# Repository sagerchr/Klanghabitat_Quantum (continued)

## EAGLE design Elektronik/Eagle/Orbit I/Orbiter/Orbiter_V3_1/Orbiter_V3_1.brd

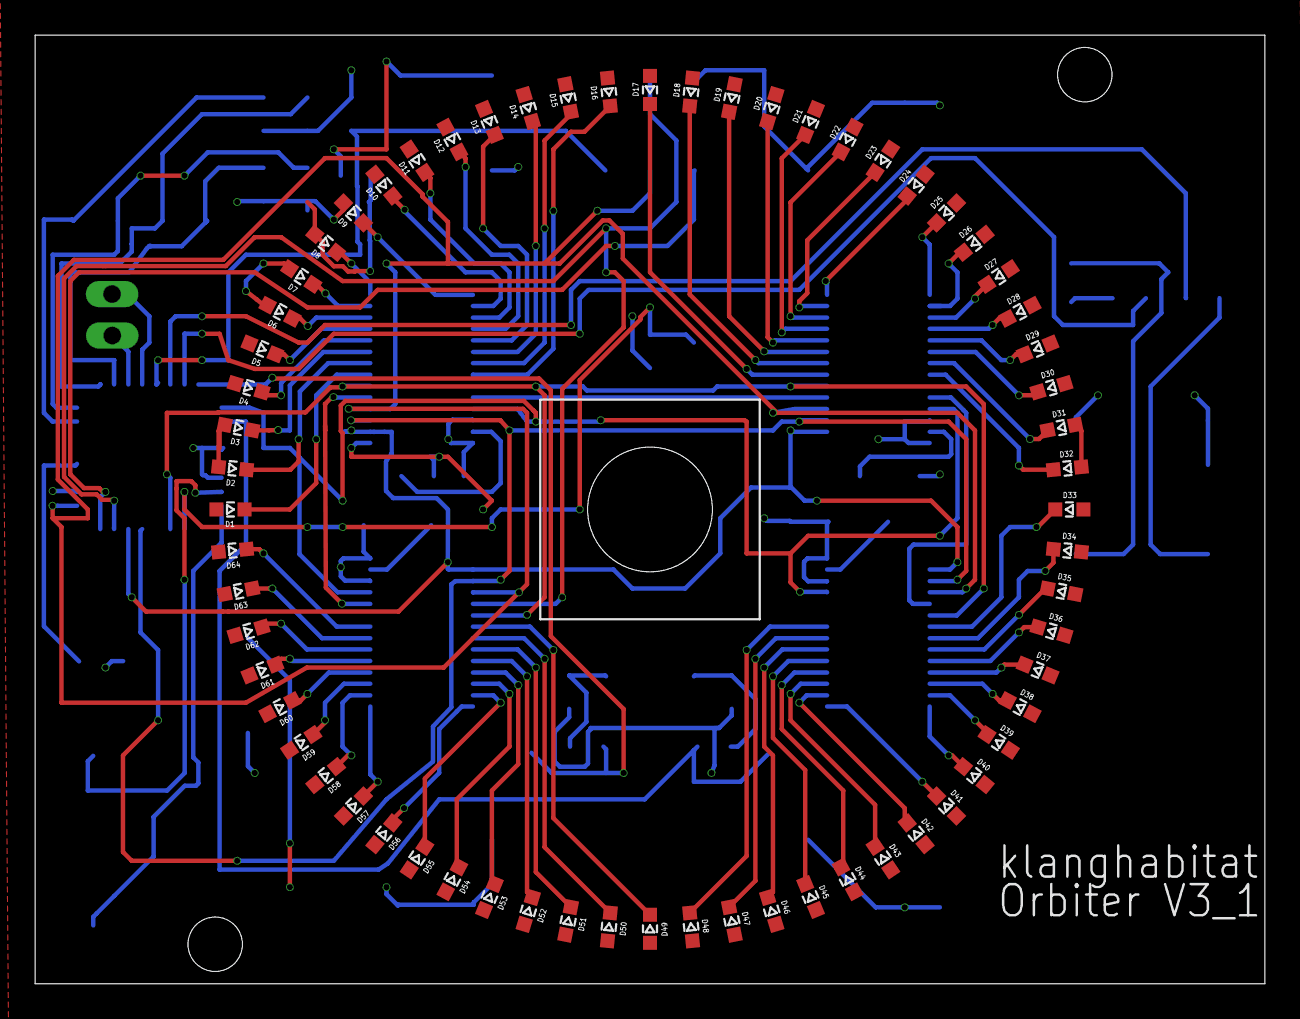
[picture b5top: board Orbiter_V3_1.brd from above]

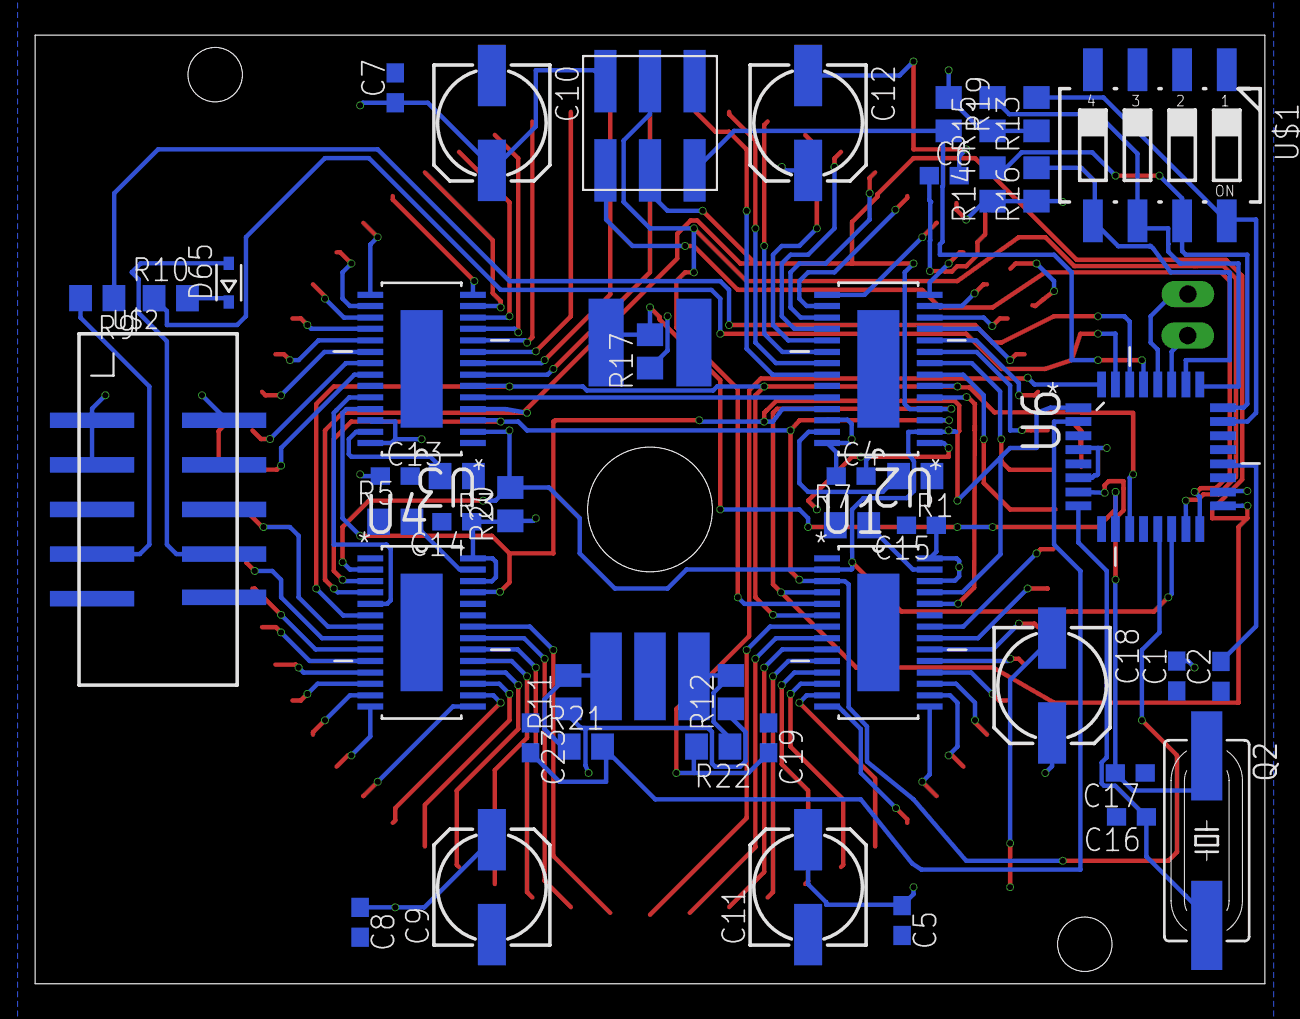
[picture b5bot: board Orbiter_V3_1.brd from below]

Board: 2 copper layers, 70.0 x 54.0 mm, 113 parts (46 on the bottom side), 100 nets.

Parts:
A4, A5: TPTHT; THT_PIN
C1: 1uF; C0603
C2: 100nF; C0603
C4, C5, C6, C7, C8, C13, C14, C15: 100n; C0603
C9, C10, C11, C12: 10u; 153CLV-0605
C16, C17: 22p; C0603
C18: 4,7uF/16V; 153CLV-0605
C19, C23: 10nF; C0603
D1, D2, D3, D4, D5, D6, D7, D8, D9, D10, D11, D12, D13, D14, D15, D16, D17, D18, D19, D20, D21, D22, D23, D24, D25, D26, D27, D28, D29, D30, D31, D32, D33, D34, D35, D36, D37, D38, D39, D40, D41, D42, D43, D44, D45, D46, D47, D48, D49, D50, D51, D52, D53, D54, D55, D56, D57, D58, D59, D60, D61, D62, D63, D64: SMD_LED_0603; WL-SMCW_0603
D65: 4148; SOD323-R
Q2: 16MHZ; SM49
R1, R3, R5, R7: 2k; R0805
R9, R10: 1k; R0805
R11, R12, R13, R14, R15, R16, R17, R19, R20, R21, R22: 10k; R0805
U1, U2, U3, U4: TLC5940; SOP65P640X120-29N
U6: ATMEGA328; QFP80P900X900X120-32N
U$1: 4PIN_DIP; CTS-219-04
U$2: 10PIN_HEADER_SMD; 87832-10
U$3: 6PIN_HEADER_SMD_OPEN
U$4: BOURNS_ENCODER; BOURNS_ENCODER_SMD

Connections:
A0: R13.2, U6.23, U$1.8
A1: R14.2, U6.24, U$1.7
A2: R15.2, U6.25, U$1.6
A3: R16.2, U6.26, U$1.5
A4: A4.P$1, U6.27
A5: A5.P$1, U6.28
D0/RX: R9.1, U6.30
D1/TX: R10.1, U6.31
D2/TB: C19.2, R22.2, U6.32
D3/GSCLK: U1.25, U2.25, U3.25, U4.25, U6.1
D4/TA: C23.2, R21.2, U6.2
D6/SWITCH: R17.2, U6.10, U$4.S2
D7/MODE: U1.6, U2.6, U3.6, U4.6, U6.11
D9/XLAT: U1.3, U2.3, U3.3, U4.3, U6.13
D10/BLANK: R20.2, U1.2, U2.2, U3.2, U4.2, U6.14
D11/MOSI/SIN: U1.5, U6.15, U$3.4
D12/MISO: U6.16, U$3.1
D13/SCK: U1.4, U2.4, U3.4, U4.4, U6.17, U$3.3
GND: C1.1, C2.1, C4.2, C5.2, C6.2, C7.2, C8.2, C9.-, C10.-, C11.-, C12.-, C13.2, C14.2, C15.2, C16.2, C17.1, C18.-, C19.1, C23.1, R1.1, R3.1, R5.1, R7.1, U1.1, U2.1, U3.1, U4.1, U6.3, U6.5, U6.21, U$1.1, U$1.2, U$1.3, U$1.4, U$2.5, U$2.6, U$2.9, U$2.10, U$3.6, U$4.S1, U$4.VDC
IREF_U1: R1.2, U2.27
IREF_U2: R3.2, U3.27
IREF_U3: R5.2, U4.27
IREF_U4: R7.2, U1.27
unnamed: D1.1, U2.7
unnamed: U1.24, U2.5
unnamed: D2.1, U2.8
unnamed: D8.1, U2.14
unnamed: D3.1, U2.9
unnamed: D9.1, U2.15
unnamed: D4.1, U2.10
unnamed: D10.1, U2.16
unnamed: D5.1, U2.11
unnamed: D6.1, U2.12
unnamed: D7.1, U2.13
unnamed: D11.1, U2.17
unnamed: D12.1, U2.18
unnamed: D13.1, U2.19
unnamed: D14.1, U2.20
unnamed: D15.1, U2.21
unnamed: D16.1, U2.22
unnamed: D17.1, U3.7
unnamed: D18.1, U3.8
unnamed: D19.1, U3.9
unnamed: D20.1, U3.10
unnamed: D21.1, U3.11
unnamed: D22.1, U3.12
unnamed: D23.1, U3.13
unnamed: D24.1, U3.14
unnamed: D25.1, U3.15
unnamed: D26.1, U3.16
unnamed: D27.1, U3.17
unnamed: D28.1, U3.18
unnamed: D29.1, U3.19
unnamed: D30.1, U3.20
unnamed: D31.1, U3.21
unnamed: D32.1, U3.22
unnamed: D33.1, U4.7
unnamed: D34.1, U4.8
unnamed: D35.1, U4.9
unnamed: D36.1, U4.10
unnamed: D37.1, U4.11
unnamed: D38.1, U4.12
unnamed: D39.1, U4.13
unnamed: D40.1, U4.14
unnamed: D41.1, U4.15
unnamed: D42.1, U4.16
unnamed: D43.1, U4.17
unnamed: D44.1, U4.18
unnamed: D45.1, U4.19
unnamed: D46.1, U4.20
unnamed: D47.1, U4.21
unnamed: D48.1, U4.22
unnamed: D49.1, U1.7
unnamed: D50.1, U1.8
unnamed: D51.1, U1.9
unnamed: D52.1, U1.10
unnamed: D53.1, U1.11
unnamed: D54.1, U1.12
unnamed: D55.1, U1.13
unnamed: D56.1, U1.14
unnamed: D57.1, U1.15
unnamed: D58.1, U1.16
unnamed: D59.1, U1.17
unnamed: D60.1, U1.18
unnamed: D61.1, U1.19
unnamed: D62.1, U1.20
unnamed: D63.1, U1.21
unnamed: D64.1, U1.22
unnamed: D65.C, R10.2
unnamed: C17.2, Q2.1, U6.7
unnamed: C16.1, Q2.2, U6.8
unnamed: C2.2, U6.20
RESET: R19.2, U6.29, U$3.5
RX: R9.2, U$2.7
SIN_U2: U2.24, U3.5
SIN_U3: U3.24, U4.5
TA: R11.2, R21.1, U$4.TA
TB: R12.2, R22.1, U$4.TB
TX: D65.A, U$2.8
VCC: C1.2, C4.1, C5.1, C6.1, C7.1, C8.1, C9.+, C10.+, C11.+, C12.+, C13.1, C14.1, C15.1, C18.+, D1.2, D2.2, D3.2, D4.2, D5.2, D6.2, D7.2, D8.2, D9.2, D10.2, D11.2, D12.2, D13.2, D14.2, D15.2, D16.2, D17.2, D18.2, D19.2, D20.2, D21.2, D22.2, D23.2, D24.2, D25.2, D26.2, D27.2, D28.2, D29.2, D30.2, D31.2, D32.2, D33.2, D34.2, D35.2, D36.2, D37.2, D38.2, D39.2, D40.2, D41.2, D42.2, D43.2, D44.2, D45.2, D46.2, D47.2, D48.2, D49.2, D50.2, D51.2, D52.2, D53.2, D54.2, D55.2, D56.2, D57.2, D58.2, D59.2, D60.2, D61.2, D62.2, D63.2, D64.2, R11.1, R12.1, R13.1, R14.1, R15.1, R16.1, R17.1, R19.1, R20.1, U1.26, U1.28, U2.26, U2.28, U3.26, U3.28, U4.26, U4.28, U6.4, U6.6, U6.18, U$2.1, U$2.2, U$2.3, U$3.2

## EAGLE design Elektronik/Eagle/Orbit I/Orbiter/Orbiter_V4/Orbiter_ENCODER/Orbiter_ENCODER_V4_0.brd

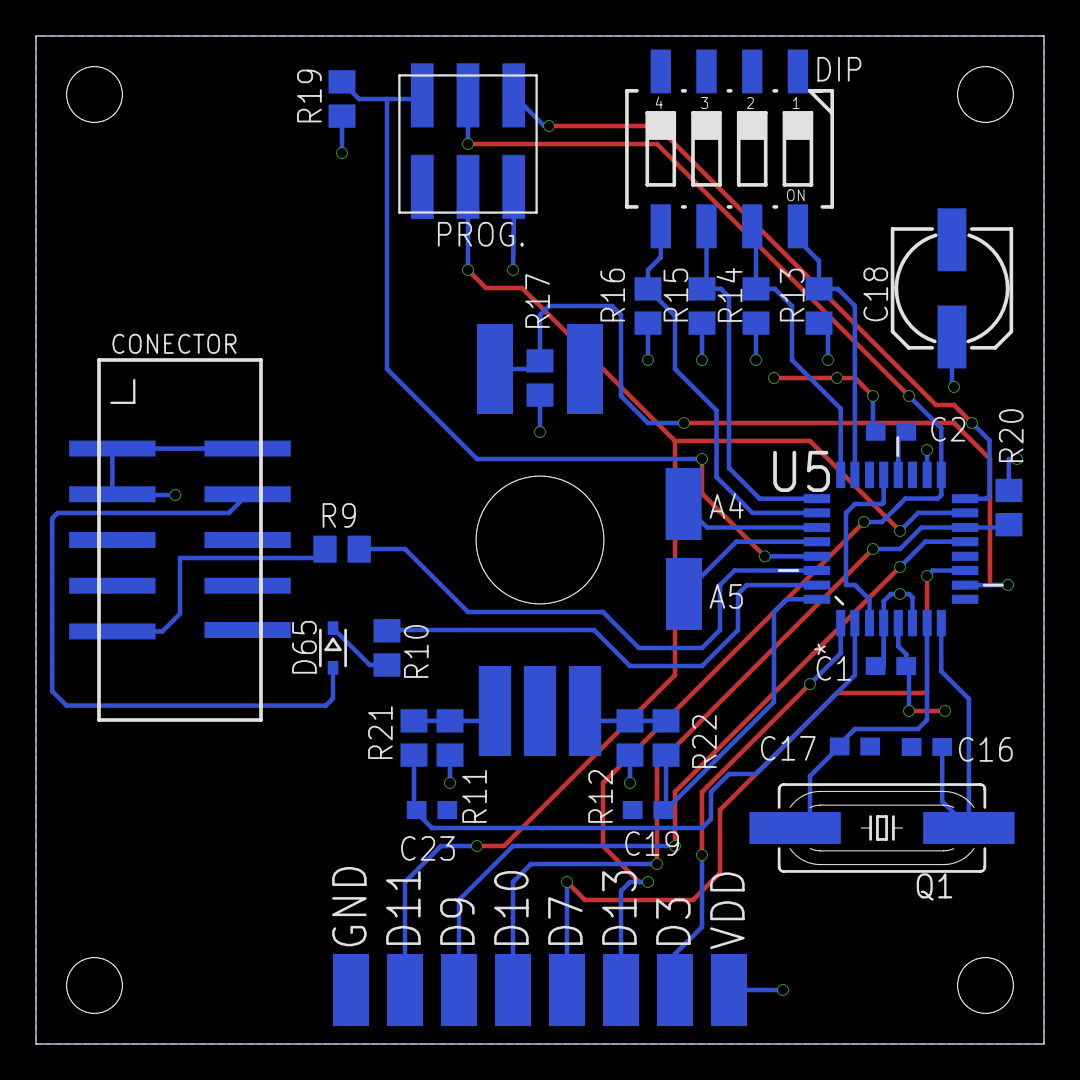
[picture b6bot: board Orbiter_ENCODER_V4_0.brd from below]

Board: 2 copper layers, 56.0 x 56.0 mm, 37 parts (36 on the bottom side), 29 nets.

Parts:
A4, A5: TP; OVAL_PAD
C1: 1uF; C0603
C2: 100nF; C0603
C16, C17: 22p; C0603
C18: 4,7uF/16V; 153CLV-0605
C19, C23: 10nF; C0603
CONECTOR: 10PIN_HEADER_SMD; 87832-10
D65: 4148; SOD323-R
DIP: 4PIN_DIP; CTS-219-04
ENC.: BOURNS_ENCODER; BOURNS_ENCODER_SMD
PROG.: 6PIN_HEADER_SMD_OPEN
Q1: 16MHZ; SM49
R9, R10: 1k; R0805
R11, R12, R13, R14, R15, R16, R17, R19, R20, R21, R22: 10k; R0805
U5: ATMEGA328; QFP80P900X900X120-32N
U$1, U$2, U$3, U$4, U$5, U$6, U$7, U$8: TP; OVAL_PAD

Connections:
A0: DIP.8, R13.2, U5.23
A1: DIP.7, R14.2, U5.24
A2: DIP.6, R15.2, U5.25
A3: DIP.5, R16.2, U5.26
A4: A4.P$1, U5.27
A5: A5.P$1, U5.28
D0/RX: R9.1, U5.30
D1/TX: R10.1, U5.31
D2/TB: C19.2, R22.2, U5.32
D3/GSCLK: U5.1, U$7.P$1
D4/TA: C23.2, R21.2, U5.2
D6/SWITCH: ENC..S2, R17.2, U5.10
D7/MODE: U5.11, U$8.P$1
D9/XLAT: U5.13, U$6.P$1
D10/BLANK: R20.2, U5.14, U$5.P$1
D11/MOSI/SIN: PROG..4, U5.15, U$4.P$1
D12/MISO: PROG..1, U5.16
D13/SCK: PROG..3, U5.17, U$3.P$1
GND: C1.1, C2.1, C16.2, C17.1, C18.-, C19.1, C23.1, CONECTOR.5, CONECTOR.6, CONECTOR.7, CONECTOR.8, CONECTOR.10, DIP.1, DIP.2, DIP.3, DIP.4, ENC..S1, ENC..VDC, PROG..6, U5.3, U5.5, U5.21, U$2.P$1
unnamed: D65.C, R10.2
unnamed: C17.2, Q1.1, U5.7
unnamed: C16.1, Q1.2, U5.8
unnamed: C2.2, U5.20
RESET: PROG..5, R19.2, U5.29
RX: CONECTOR.9, R9.2
TA: ENC..TA, R11.2, R21.1
TB: ENC..TB, R12.2, R22.1
TX: CONECTOR.4, D65.A
VDD: C1.2, C18.+, CONECTOR.1, CONECTOR.2, CONECTOR.3, PROG..2, R11.1, R12.1, R13.1, R14.1, R15.1, R16.1, R17.1, R19.1, R20.1, U5.4, U5.6, U5.18, U$1.P$1
